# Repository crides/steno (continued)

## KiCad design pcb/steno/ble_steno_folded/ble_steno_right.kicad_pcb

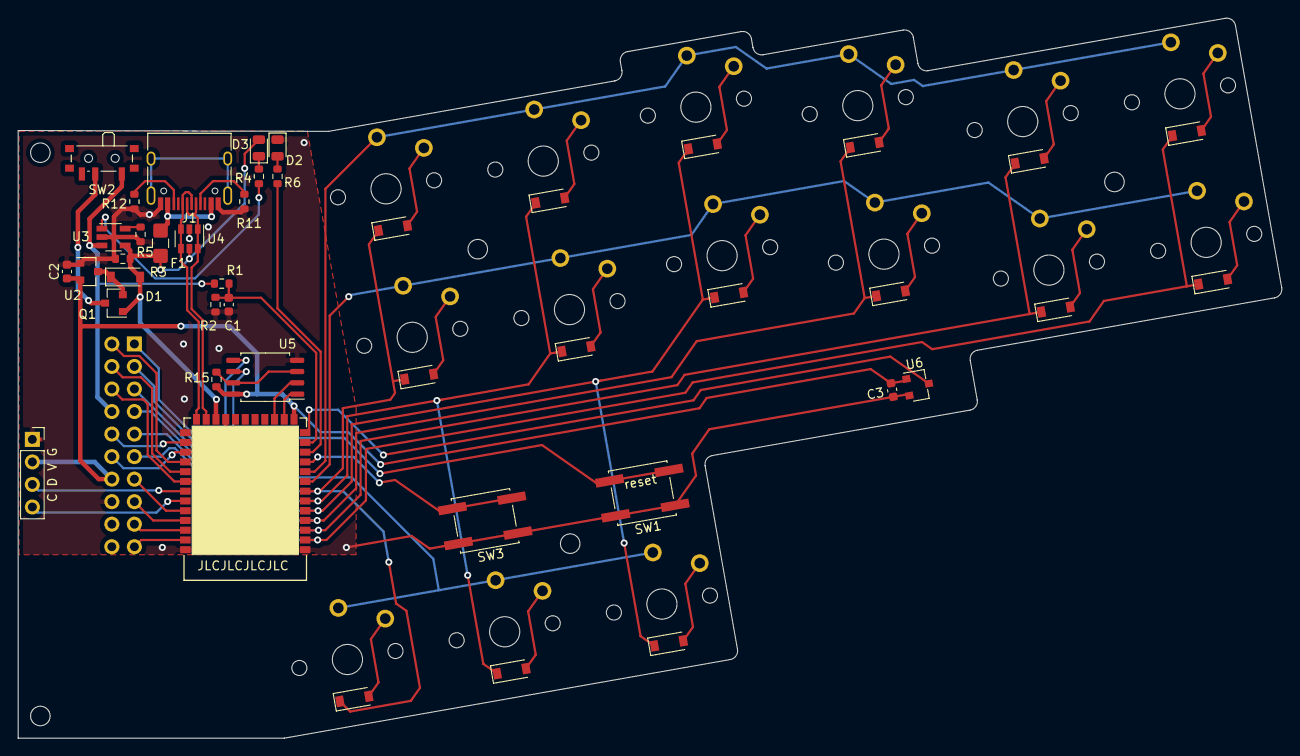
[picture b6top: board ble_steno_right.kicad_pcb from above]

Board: 2 copper layers, 142.5 x 81.2 mm, 44 parts (1 on the bottom side), 42 nets.

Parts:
C1: 10nF; C_0603_1608Metric
C2: 1uF; C_0603_1608Metric
C3: 0.1uF; C_0603_1608Metric
D1: 1N5819; D_SOD-123
D2: BLUE; LED_0805_2012Metric
D3: RED; LED_0805_2012Metric
F1: Polyfuse_Small; Fuse_1206_3216Metric_Castellated
J1: USB_C_Receptacle_USB2.0; USB_C_Receptacle_HRO_TYPE-C-31-M-12
J2: Conn_02x10_Odd_Even; PinHeader_2x10_P2.54mm_Horizontal
J4: Conn_01x04_Female; PinSocket_1x04_P2.54mm_Vertical
K1, K2, K3, K4, K5, K6, K7, K8, K9, K10, K11, K12, K13, K14, K15: 1N4148W; PG1350
Q1: AO3401A; SOT-23
R1, R2: 2M; R_0603_1608Metric
R3: 100k; R_0603_1608Metric
R4, R6: 1k; R_0603_1608Metric
R5, R15: 10k; R_0603_1608Metric
R11, R12: 5.1k; R_0603_1608Metric
SW1, SW3: SW_Push; SW_SPST_EVQQ2
SW2: SW_SPDT; SW_SPDT_PCM12
U1: Holyiot_18010_no_underside
U2: MCP1700-3302E_SOT23; SOT-23
U3: LTC4054ES5-4.2; TSOT-23-5
U4: SRV05-4; SOT-23-6
U5: MT25QL128ABA1ESE; SOP-8_5.28x5.23mm_P1.27mm
U6: AH1806-W; SC-59

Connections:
BAT: J2.8, R1.1, SW2.1, U3.3
BAT_MEAS: C1.1, R1.2, R2.1, U1.12
BLUE: R6.1, U1.11
BTN: SW3.2, U1.10
COL1: J2.11, K6.2, K12.2, U1.2
COL2: J2.9, K5.2, K11.2, U1.3
COL3: J2.7, K4.2, K10.2, U1.4
COL4: J2.5, K3.2, K9.2, K15.2, U1.5
COL5: J2.3, K2.2, K8.2, K14.2, U1.6
COL6: J2.1, K1.2, K7.2, K13.2, U1.7
D+: J1.A6, J1.B6, U1.45, U4.3, U4.4
D-: J1.A7, J1.B7, U1.46, U4.1, U4.6
FLASH_CS: U1.54, U5.1
GND: C1.2, C2.2, C3.2, D2.1, J1.A1, J1.A12, J1.B1, J1.B12, J2.16, J4.1, R2.2, R3.2, R5.2, R11.1, R12.1, SW1.1, SW3.1, U1.1, U1.32, U1.44, U2.1, U3.2, U4.2, U5.4, U6.2
LCD_CS: J2.19, U1.33
LCD_DISP: J2.15, U1.35
LCD_EIN: J2.13, U1.36
LCD_EMD: J2.17, U1.34
MAGNET: U1.13, U6.3
MCU_BAT: Q1.3, SW2.2
MISO_DQ1: U1.53, U5.2
MOSI_DQ0: J2.10, U1.43, U5.5
unnamed: D1.1, Q1.2, U2.3
unnamed: D2.2, R6.2
unnamed: D3.1, R4.2
unnamed: J1.A5, R11.2
unnamed: J1.B5, R12.2
unnamed: R4.1, U3.1
unnamed: R5.1, U3.5
unnamed: R15.2, U5.3, U5.7
ROW1: J2.2, U1.41
ROW2: J2.4, U1.40
ROW3: J2.6, K13.1, K14.1, K15.1, U1.39
ROW4: K1.1, K2.1, K3.1, K4.1, K5.1, K6.1, U1.9
ROW5: K7.1, K8.1, K9.1, K10.1, K11.1, K12.1, U1.8
RST: SW1.2, U1.48
SCLK: J2.12, U1.42, U5.6
SWC: J4.4, U1.37
SWD: J4.3, U1.38
VBUS: D1.2, D3.2, F1.1, Q1.1, R3.1, U1.47, U3.4, U4.5
VCC: F1.2, J1.A4, J1.A9, J1.B4, J1.B9
VDD: C2.1, C3.1, J2.14, J4.2, R15.1, U1.55, U2.2, U5.8, U6.1

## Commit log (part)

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2020-03-28 Trimming code
    Removed card detection pins; we don't have enough I/O
    Forced enabled SDHC support
    Changed CS pins, removed unneeded conditional compilations
2020-03-28 Rename folders
2020-03-29 Single stage demo
2020-03-29 Add link time optimization for firmware sizes
2020-03-30 Finished multisearch; Starting on undoing
2020-04-25 Moved the whole compile process to rust
2020-04-29 Assuming FAT blocks are continuous
    Previously, the FAT library has to read the File Allocation Table to
    determine the next block of the file. Obviously that is not cached, so
    retrieving the next block address has a very high overhead. Since for
    now the blocks seems to be continuous, we'll assume that until we have a
    new design that uses a SPI flash and USB Mass Storage
2020-05-03 Change format to HashMap
2020-05-08 Refractor into modules
2020-05-10 Revamp history
    Search nodes recovery is working
2020-05-11 Implemented Plover command conversion
    ... But in a crappy way ... For now
2020-05-11 Get rid of `max_level_ended`
2020-05-11 Add states and attrs for Plover commands
2020-05-11 Add .gitignore for compiler
2020-05-12 Move number glue check from firmware to compiler
    In Plover, an entry is automatically glued if everything is digit. Since
    the digit implementation came before the attributes, this was done in
    firmware. As something like this is static, we move it into the
    compiler.
2020-05-18 Add v2 gerber
2020-05-18 Fix undo bug
    Also changes from `uprintf` to `xprintf`
2020-05-21 Changed `Stroke` string converstion to be same on MCU
2020-05-21 Move collision stats outside; cargo fmt
2020-05-22 More attribute parsing done!
    - Separated Rust and C attribute handling
    - Reorganized compilation related types to `compile.rs`
    - Changed node hashing to using first level children
    - Added simple tests for entry parsing
2020-05-22 Change API to match Rust side
2020-05-23 Pseudo fixed spacing bugs
    - ... By pseudo merging the attribute-only atoms together in an entry
    (i.e. no space between, and joining the attributes (primarily for
    `{}{-|}`)).
    - Added more tests.
2020-05-23 Add custom forked libraries for HID
2020-05-23 client test code
2020-05-25 Ignore unused parameters
2020-05-25 Fix node searching bug
    This bug currently affects words with default orthography, i.e. the ones
    that you just add a s to it, for example. This bug is discovered with
    the stroke sequence REBG/ORD/S, which should output "records", but
    was outputting "orders", as there's no orthography rules for "record"
    because you just need to add s to it, and the engine sees that "orders"
    is the longest match, and uses it.
2020-05-28 Fix node searching bugs
    - Change when max level node ends. Instead of checking number of
    children of a certain node, we now skip the rest of the search nodes
    if we can't find the next node for a certain node, and go straight for
    the root node. This also resolves the problem in b7e2e90, which is
    manually reverted.
    - Fix variable declaration in header
2020-05-29 Small bug fixes and refractoring
2020-05-29 Basic keycodes support in compiler
2020-05-30 Optimize log messages and other small fixes
2020-05-31 Add flashing commands and progress bars
2020-05-31 Update C lib
2020-06-02 Remove draw_delta
2020-06-02 Optimize
2020-06-04 Firmware: Add MassWrite handling
2020-06-04 Change to crc8 and other optimizations
2020-06-04 Separate bytes and normal progress bars
2020-06-06 Firmware: Move debugging functionalities; Simplify searching algo
2020-06-06 Optimization: no string header when entry is only string
    Since most of the entries are not using key codes, the string header is
    useless. So we get rid of that, and we can just use the entry_len as the
    string length.
2020-06-13 Change keycode support in firmware
2020-06-14 Searching bug
2020-06-14 Update PCB
2020-06-14 Routed and plotted v3
2020-06-24 Fix str-only logic; fix startup caps
2020-06-29 Simple code level documentations
2020-07-22 Mobile steno
2020-07-22 Add README
2020-07-22 Add nrf52840 files
2020-08-01 Add stenophone firmware and small refractor debugging util
2020-08-04 Refractor firmware debugging
2020-08-11 Switch to `onig` from `regex`
2020-08-17 Add usage instructions
2020-08-18 Create LICENSE
2020-09-28 First PCB version
    - Use raw MCU
    - Use 5x6 matrix and 30keys (like steno phone)
    - Use SOD-123 diodes (like steno phone)
    - Use 2.2in TFT for better UX(?)
    - Lots of ground plane!
    - Add (fake?) logo and contributors
2020-10-12 [compiler] Change entry format
    - Flatten entry structure
    - Move caps stuff from attributes to commands
2020-10-12 [firmware] Add basic LCD support
    - Adopted LCD library from `adafruit/Adafruit_ILI9341` and
    `adafruit/Adafruit-GFX-Library`
    - Refractored SPI stuff out from flash
    - Still need to clean up bits (e.g. last stroke/translation stuff, which was
    related to OLED)
2020-10-18 [firmware] Fix unicode and start implementing dict_edit ui
2020-10-22 [dict] Minor dictionary changes
2020-10-23 [compiler] First steps towards new format
    Changing compiler to compile to flat hashmap structure. Divide the
    storage into 3 sections, 1 for buckets in the hash map, 1 for key value
    pairs, and the final one for keeping track of use the used blocks if the
    key value pairs section.
    Main remaining issues:
    - Block free mop still need to be added to the final compiled
2020-10-24 [dict] Remove some fingerspell entries & recompile for new format
2020-10-24 [firmware] Use Mass Storage & ghostfat for firmware upload
    Prerequisite: patch from QMK that enables MSC
    - Pull in SCSI handling files from LUFA example
    - Pull in and adapting ghostfat from Adafruit nRF52 bootloader
2020-10-26 [firmware] Add basic dictionary editing code
2020-10-29 [firmware] rev2 hardware pin mappings
2020-11-04 [compiler] Fix issues and add utils
    - Compiling: swap length & attribute (length in front)
    - CLI: add hash strokes for testing
    - Dict parsing: add more test cases & make pure numbers glue
    - Stroke: make multiplication explicitly wrapping
2020-11-08 [firmware] add dictionary adding/removing code
2020-11-08 update editing code
2020-11-09 [firmware] Macro-ize some dict operations & add (untested) freemap allocator
2020-11-11 [firmware] Optimize LCD parts
    - Macro-ize constants
    - Minimizing calls in `vline`, `hline`, and `fill_rect` by using
    `set_addr_window` properly
    - Cut out unused font data
2020-11-11 [firmware] add dict editing UI
2020-11-11 [firmware] Macro-ize things
2020-11-11 [firmware] Fix dict entry removing
2020-11-13 [compiler] Fix allocator & use UF2 file format
2020-11-14 [compiler] Fix block allocator
2020-11-18 [compiler] Slightly modify UF2 file format for easier handling
2021-02-14 [firmware] Move entry length to bucket + small refractors
2021-02-14 [compiler] Move entry size to bucket
2021-02-15 [PCB] Use "raw" LCD + backside components
2021-02-18 [firmware] bug fixes + refractor
    - Fix some leftover incorrect assumptions when moving entry length into
    buckets
    - Rename `entry(_ptr)` to `bucket`
    - Remove sekigon QMK stuff
    - Remove SD card and (true) FAT support files
2021-03-02 [PCB] Remove unused footprint and gerbers
2021-03-14 [PCB] Public test version
2021-03-14 [PCB] Update paths
2021-03-29 [firmware] Fix keep case bug
2021-04-15 [firmware] Refractor
    - Made term naming more coherent. Previously `entry` has ambiguous
    meaning
    * KVpair: the valid part of a allocated block, which a bucket points
    to
    * Entry: the part of a KVpair after the strokes
    - Abstracts the stroage (currently flash), UI/display, and keyboard
2021-04-18 [firmware] Feature: Graphical stroke display
    A simple graphical stroke display at the bottom of the screen for
    demoing purposes. Uses messy and (slightly) inefficient drawing
    Also simplifies the paper tape display interface
2021-04-19 [docs] Update firmware docs
    - includes more instructions
    - update to reflect new dictionary editing system and remove old junk
2021-04-19 [firmware] New dictionary editing interface
    Merged the 3 commands into one, with a for-the-moment simple UI design
2021-04-24 [firmware] Ditch QMK steno and use custom keycodes
2021-04-24 [compiler] Add compiled simple rules
    - Remove word list cuz we can't use that anywhere
    - Compile simple rules (exception from regex rules) into 64KiB sized binary hashmap
    - Rules comes from https://github.com/nimble0/dotterel/blob/master/app/src/main/assets/orthography/english.simple.json
    - Load rules at `0xF30000`
2021-04-27 compiler compile err msg
2021-04-27 compiler fix err msg
2021-04-29 larger drive
2021-04-29 timing benchmarks
2021-05-02 correct \\{ compiling
2021-05-15 raw stroke undo
2021-05-15 Add flash based logging.
    Starts at 0xF80000 in flash, uses 4 bytes @ 128 in EEPROM to store
    logging address
2021-05-15 ortho fix
2021-05-17 GhostFAT hacks to make `fsck.fat` seemingly happy?
2021-05-19 [compiler] Basic parsing
2021-05-19 [firmware] Allow right side mods
2021-05-19 [firmware] Config refractor
    Concentrate all the configs into `config.mk`, and use `rules.mk` as
    config processing
2021-05-19 [compiler] Use nom for entry parsing
    - Some parts of `lalrpop` doesn't work properly, so we use `nom` for the
    moment
    - Ignoring (i.e. not including) entries that can't be parsed
    clippy
2021-05-19 [firmware] Add flash based logging
    Starts at 0xF80000 in flash, uses 4 bytes @ 128 in EEPROM to store
    logging address
2021-05-26 Option to disable internal orthography engine
2021-05-28 Rework flash/console logging
2021-06-18 don't force keycodes to be ident
2021-06-18 Fix space between keys
2021-06-18 firmware fix double key up; hack?
2021-06-18 uhhhh
2021-06-22 suffix folding; should be same as Plover
    somewhat hacky. duplicate code between this and normal orthography.
    should be optimized/cleaned up in later commits
2021-06-22 compiler allow 256 kv pairs
2021-06-28 ZMK add remaining files
2021-06-28 zmk use primitive keypress
2021-07-20 UI configs?
2021-07-20 ZMK dictionary editing UI
2021-07-20 zmk better Kconfig?
2021-07-21 zmk empty stroke bug
2021-07-22 zmk log on flash error
2021-07-22 [PCB] Add folded bat design and production files
2021-07-22 [firmware] rework configs
    - add option to disable internal orthography engine
    - rework flash/console logging
2021-07-22 [compiler] make dict patching a feature
    Dictionary patching is no longer needed by default, as the internal
    orthography engine should do the work. But this is left in as a feature
    so that experiments can be done easily
2021-07-22 [fw.zmk] basic ZMK support
    - no UI
    - use keyboard name `define`s (i.e. `QMK_KEYBOARD` &
    `CONFIG_ZMK_KEYBOARD_NAME`) to distinguish platforms
2021-07-22 [fw] add suffix folding
    behavior should be same as Plover
    Somewhat hacky. There are some duplicate code between this and normal
    orthography handling code, should be optimized/cleaned up in later
    commits
    janky fix
2021-07-22 [fw.zmk] add ringbuf check
2021-07-22 [fw.zmk] basic paper tape UI
2021-07-22 [fw.zmk] use `/chosen` node for spi flash
    use the `zmk,steno_flash` property to denote what flash driver to use,
    as there can be multiple different types of flash drivers and the flash
    can also live on different buses (QSPI vs. normal SPI)
2021-07-22 [fw.zmk] fix empty stroke bug
2021-07-24 [fw] resolve uninit problems
2021-10-12 [fw] show git hash on startup
2021-10-21 compiles
2021-10-27 [compiler] update dependencies
2021-10-27 ortho: pre cond
2021-10-28 custom verification
2021-11-07 pend: clause
2021-11-15 pending: dict
2021-11-27 static
2021-12-03 C ortho test w/ onig
2021-12-03 add `ortho-veri`
2021-12-26 [pcb] update libraries
2021-12-27 [pcb] Auklet 3
2021-12-31 [pcb] auklet 3: use new libraries
2022-01-08 [pcb] Plutonium: first revision
2022-01-08 [pcb] Auklet 3: first revision
2022-01-09 [pcb] Update `kleeb`
2022-01-09 [pcb] Auklet: add tooling holes
2022-01-28 change downloading pin
2022-01-31 fix matrix
2022-02-10 seahorn test
2022-02-14 dict
2022-02-14 add(auklet): board cover
2022-03-25 freemap: cpa mock setup
2022-03-28 fix(auklet): update RGB
2022-03-30 lshift workaround
2022-04-03 revert workarounds
2022-12-19 fw.zmk: update for zephyr 3.2 (?)
2022-12-22 back cover
